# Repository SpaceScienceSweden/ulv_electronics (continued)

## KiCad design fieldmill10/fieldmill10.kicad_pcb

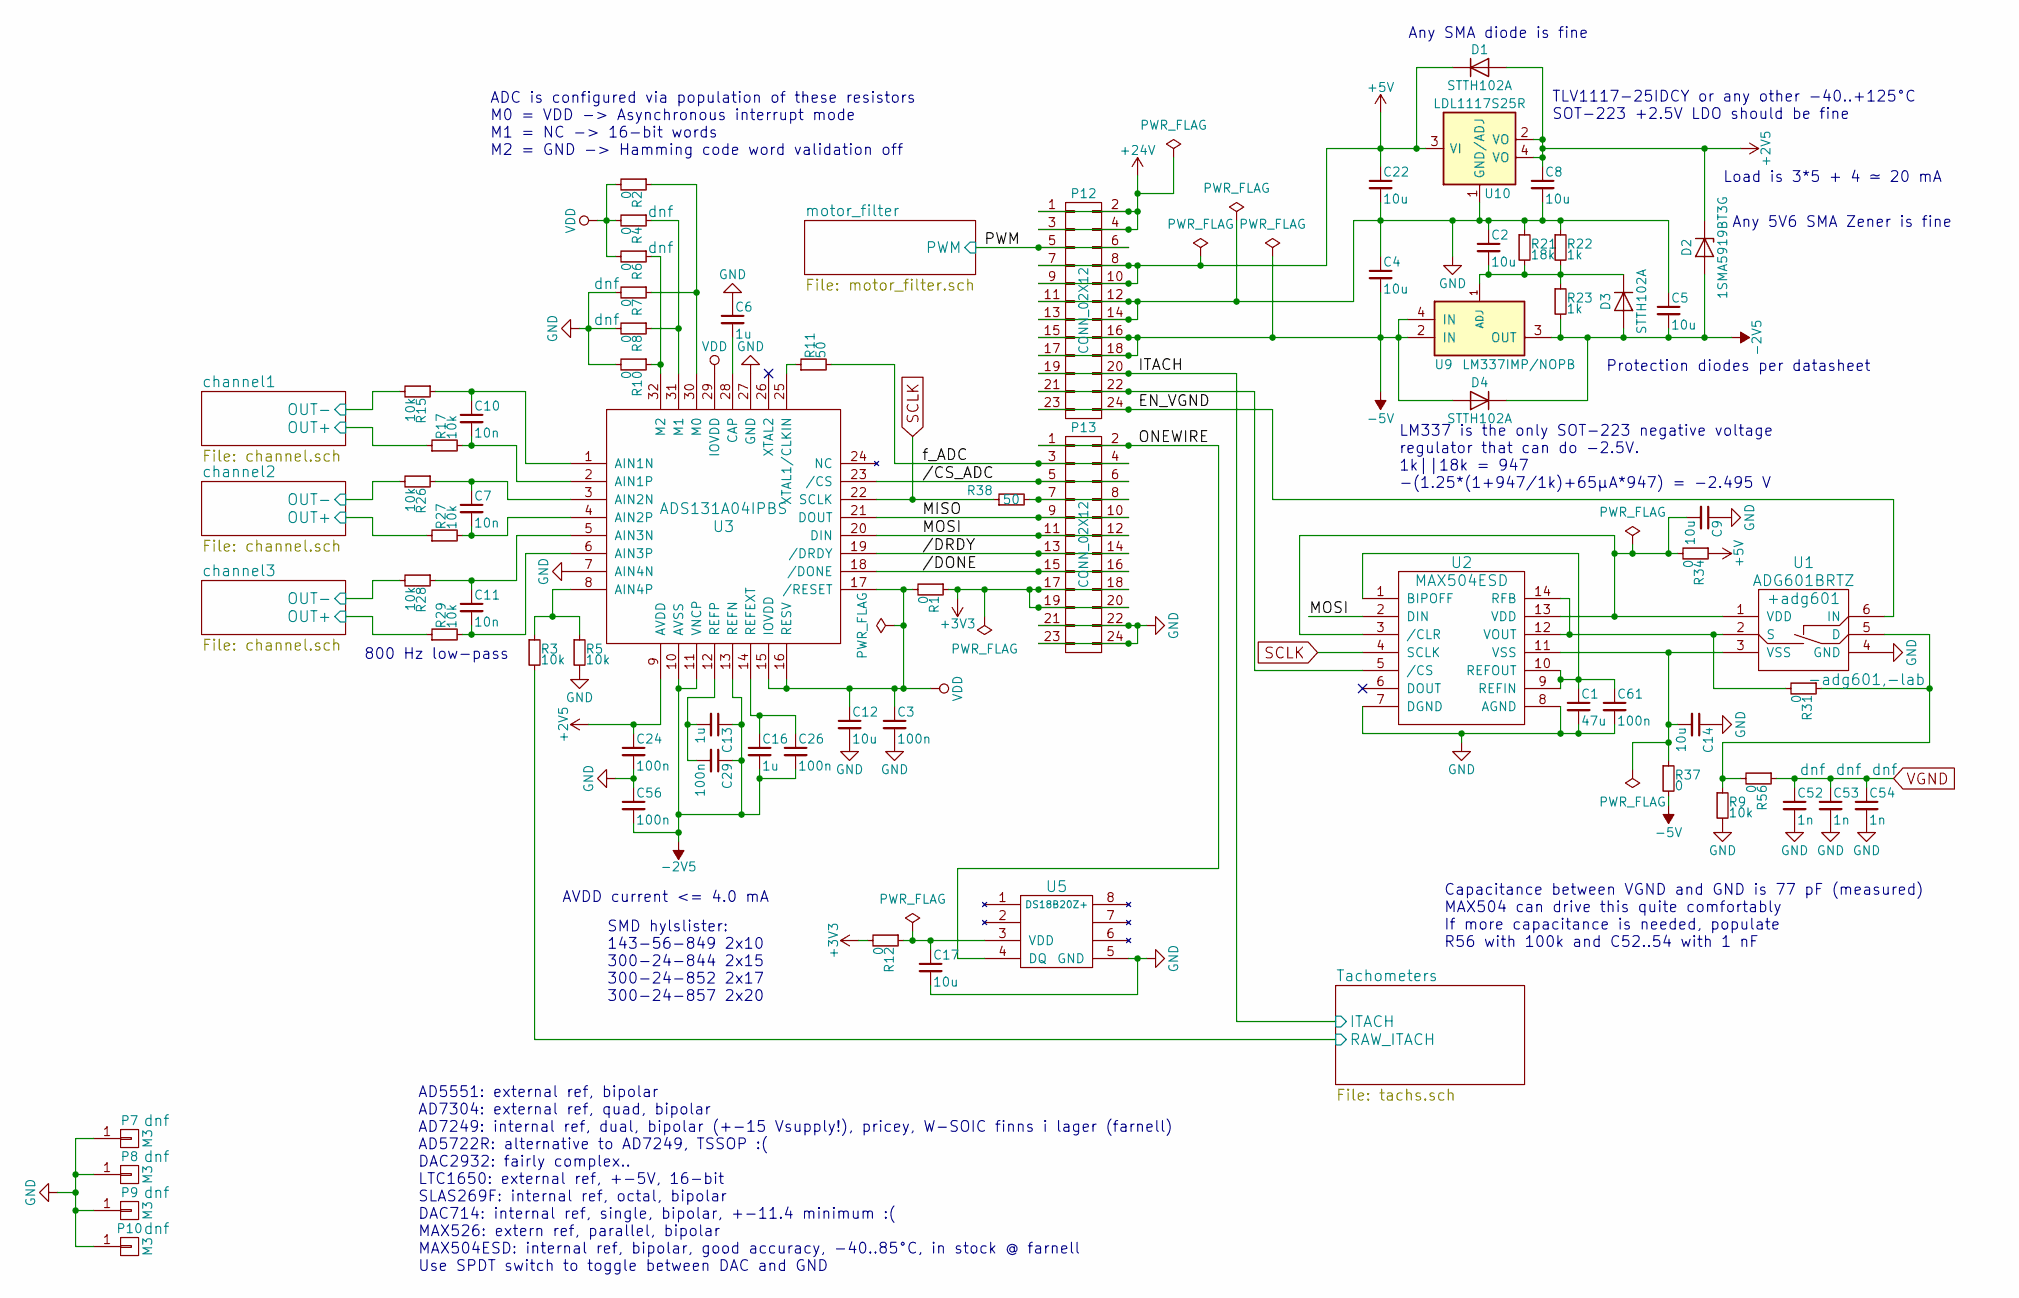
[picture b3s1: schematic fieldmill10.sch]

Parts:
C1: 47u; C_1210; Mfg. Part Number GCJ32ER70J476KE01L; Mouser PN 81-GCJ32ER70J476KE1L
C2, C4, C5, C9, C12, C14, C17, C22: 10u; C_0805; Mfg. Part Number C0805X106M8RACAUTO; Farnell PN 2776919
C3, C24, C26, C29, C56, C61: 100n; C_1210; Mfg. Part Number ECH-U1C104GX5; Farnell PN 9695001
C6, C13, C16: 1u; C_0805; Mfg. Part Number C0805X105K3RACAUTO; Farnell PN 2478267
C7, C10, C11: 10n; C_0805; Mfg. Part Number ECH-U1C103GX5; Farnell PN 9694897
C8: 10u; C_0805
C52, C53, C54: 1n; C_0805
D1, D3, D4: STTH102A; SMA_Standard; Mfg. Part Number STTH102A; Farnell PN 9907874
D2: 1SMA5919BT3G; SMA_Standard; Mfg. Part Number 1SMA5919BT3G; Farnell PN 1431141
P7, P8, P9, P10: M3; M3_FM_PTH
P12: CONN_02X12; LPPB122NFSP-RC-holes; Mfg. Part Number LPPB122NFSP-RC; Digikey PN S9007E-12-ND
P13: CONN_02X12; LPPB122NFSP-RC-holes
R1, R12, R34, R37: 0; R_1206
R2, R4, R6, R7, R8, R10, R31, R56: 0; R_0805
R3, R5, R9, R15, R17, R26, R27, R28, R29: 10k; R_0805
R11, R38: 50; R_0805
R21: 18k; R_0805
R22, R23: 1k; R_0805
U1: ADG601BRTZ; SOT-23-6; Mouser PN 584-ADG601BRTZ-R7; Farnell PN 1661035
U2: MAX504ESD; SOIC-14_3.9x8.7mm_Pitch1.27mm; Mfg. Part Number MAX504ESD+; Farnell PN 2514723
U3: ADS131A04IPBS; LQFP-32_5x5mm_Pitch0.5mm; Mfg. Part Number ADS131A04IPBS; Farnell PN 2580620
U5: DS18B20Z+; SOIC-8_3.9x4.9mm_Pitch1.27mm; Mfg. Part Number DS18B20Z+; Farnell PN 2518724
U9: LM337IMP/NOPB; SOT-223; Mfg. Part Number LM337IMP/NOPB; Farnell PN 2781817
U10: LDL1117S25R; SOT-223; Mfg. Part Number LDL1117S25R; Farnell PN 2778100

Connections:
+2V5: C8.1, C24.1, D1.2 (A), D2.1 (K), U3.9 (AVDD), U10.2 (VO), U10.4 (VO); also elsewhere on the board
+3V3: P13.17, P13.18, P13.19, P13.20, R1.1, R12.2; also elsewhere on the board
+5V: C22.1, D1.1 (K), P12.7, P12.8, P12.9, P12.10, R34.1, U10.3 (VI)
+24V: P12.1, P12.2, P12.3, P12.4; also elsewhere on the board
-2V5: C5.2, C13.1, C16.2, C26.2, C29.1, C56.2, D2.2 (A), D3.2 (A), D4.1 (K), R23.2, U3.10 (AVSS), U3.11 (VNCP), U3.13 (REFN), U9.3 (OUT); also elsewhere on the board
-5V: C4.2, D4.2 (A), P12.15, P12.16, P12.17, P12.18, R37.2, U9.2 (IN), U9.4 (IN); also elsewhere on the board
//CS_ADC: P13.5, P13.6, U3.23 (/CS)
//DONE: P13.15, P13.16, U3.18 (/DONE)
//DRDY: P13.13, P13.14, U3.19 (/DRDY)
/EN_VGND: P12.23, P12.24, U1.6 (IN)
/ITACH: P12.19, P12.20; also elsewhere on the board
/MISO: P13.9, P13.10, U3.21 (DOUT)
/MOSI: P13.11, P13.12, U2.2 (DIN), U3.20 (DIN)
/ONEWIRE: P13.1, P13.2, U5.4 (DQ)
/PWM: P12.5, P12.6; also elsewhere on the board
/Tachometers/RAW_ITACH: R3.2; also elsewhere on the board
/channel1/OUT+: R17.1; also elsewhere on the board
/channel1/OUT-: R15.2; also elsewhere on the board
/channel2/OUT+: R27.1; also elsewhere on the board
/channel2/OUT-: R26.2; also elsewhere on the board
/channel3/OUT+: R29.1; also elsewhere on the board
/channel3/OUT-: R28.2; also elsewhere on the board
/f_ADC: P13.3, P13.4, R11.2
GND: C1.2, C2.1, C3.2, C4.1, C5.1, C6.1, C8.2, C9.1, C12.2, C14.1, C17.2, C22.2, C24.2, C52.2, C53.2, C54.2, C56.1, C61.2, P7.1, P8.1, P9.1, P10.1, P12.11, P12.12, P12.13, P12.14, P13.21, P13.22, P13.23, P13.24, R5.2, R7.2, R8.2, R9.2, R10.2, R21.1, R22.1, U1.4 (GND), U2.7 (DGND), U2.8 (AGND), U3.7 (AIN4N), U3.27 (GND), U5.5 (GND), U10.1 (GND/ADJ); also elsewhere on the board
unnamed: C1.1, C61.1, U2.1 (BIPOFF), U2.9 (REFIN), U2.10 (REFOUT)
unnamed: C2.2, D3.1 (K), R21.2, R22.2, R23.1, U9.1 (ADJ)
unnamed: C6.2, U3.28 (CAP)
unnamed: C7.1, R26.1, U3.3 (AIN2N)
unnamed: C7.2, R27.2, U3.4 (AIN2P)
unnamed: C9.2, R34.2, U1.1 (VDD), U2.3 (/CLR), U2.13 (VDD)
unnamed: C10.1, R15.1, U3.1 (AIN1N)
unnamed: C10.2, R17.2, U3.2 (AIN1P)
unnamed: C11.1, R28.1, U3.5 (AIN3N)
unnamed: C11.2, R29.2, U3.6 (AIN3P)
unnamed: C13.2, C29.2, U3.12 (REFP)
unnamed: C14.2, R37.1, U1.3 (VSS), U2.11 (VSS)
unnamed: C16.1, C26.1, U3.14 (REFEXT)
unnamed: C17.1, R12.1, U5.3 (VDD)
unnamed: P12.21, P12.22, U2.5 (/CS)
unnamed: P13.7, P13.8, R38.2
unnamed: R2.1, R7.1, U3.30 (M0)
unnamed: R3.1, R5.1, U3.8 (AIN4P)
unnamed: R4.1, R8.1, U3.31 (M1)
unnamed: R6.1, R10.1, U3.32 (M2)
unnamed: R11.1, U3.25 (XTAL1/CLKIN)
unnamed: R9.1, R31.1, R56.2, U1.5 (D)
unnamed: R31.2, U1.2 (S), U2.12 (VOUT), U2.14 (RFB)
SCLK: R38.1, U2.4 (SCLK), U3.22 (SCLK)
VDD: C3.1, C12.1, R1.2, R2.2, R4.2, R6.2, U3.15 (IOVDD), U3.16 (RESV), U3.17 (/RESET), U3.29 (IOVDD)
VGND: C52.1, C53.1, C54.1, R56.1; also elsewhere on the board

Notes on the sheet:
ADC is configured via population of these resistors M0 = VDD -> Asynchronous interrupt mode M1 = NC -> 16-bit words M2 = GND -> Hamming code word validation off
800 Hz low-pass
SMD hylslister: 143-56-849 2x10 300-24-844 2x15 300-24-852 2x17 300-24-857 2x20
AVDD current <= 4.0 mA
AD5551: external ref, bipolar AD7304: external ref, quad, bipolar AD7249: internal ref, dual, bipolar (+-15 Vsupply!), pricey, W-SOIC finns i lager (farnell) AD5722R: alternative to AD7249, TSSOP :( DAC2932: fairly complex.. LTC1650: external ref, +-5V, 16-bit SLAS269F: internal ref, octal, bipolar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
Capacitance between VGND and GND is 77 pF (measured) MAX504 can drive this quite comfortably If more capacitance is needed, populate R56 with 100k and C52..54 with 1 nF
TLV1117-25IDCY or any other -40..+125°C SOT-223 +2.5V LDO should be fine
Load is 3*5 + 4 ≃ 20 mA
LM337 is the only SOT-223 negative voltage regulator that can do -2.5V. 1k||18k = 947 -(1.25*(1+947/1k)+65µA*947) = -2.495 V
Protection diodes per datasheet
Any SMA diode is fine
Any 5V6 SMA Zener is fine

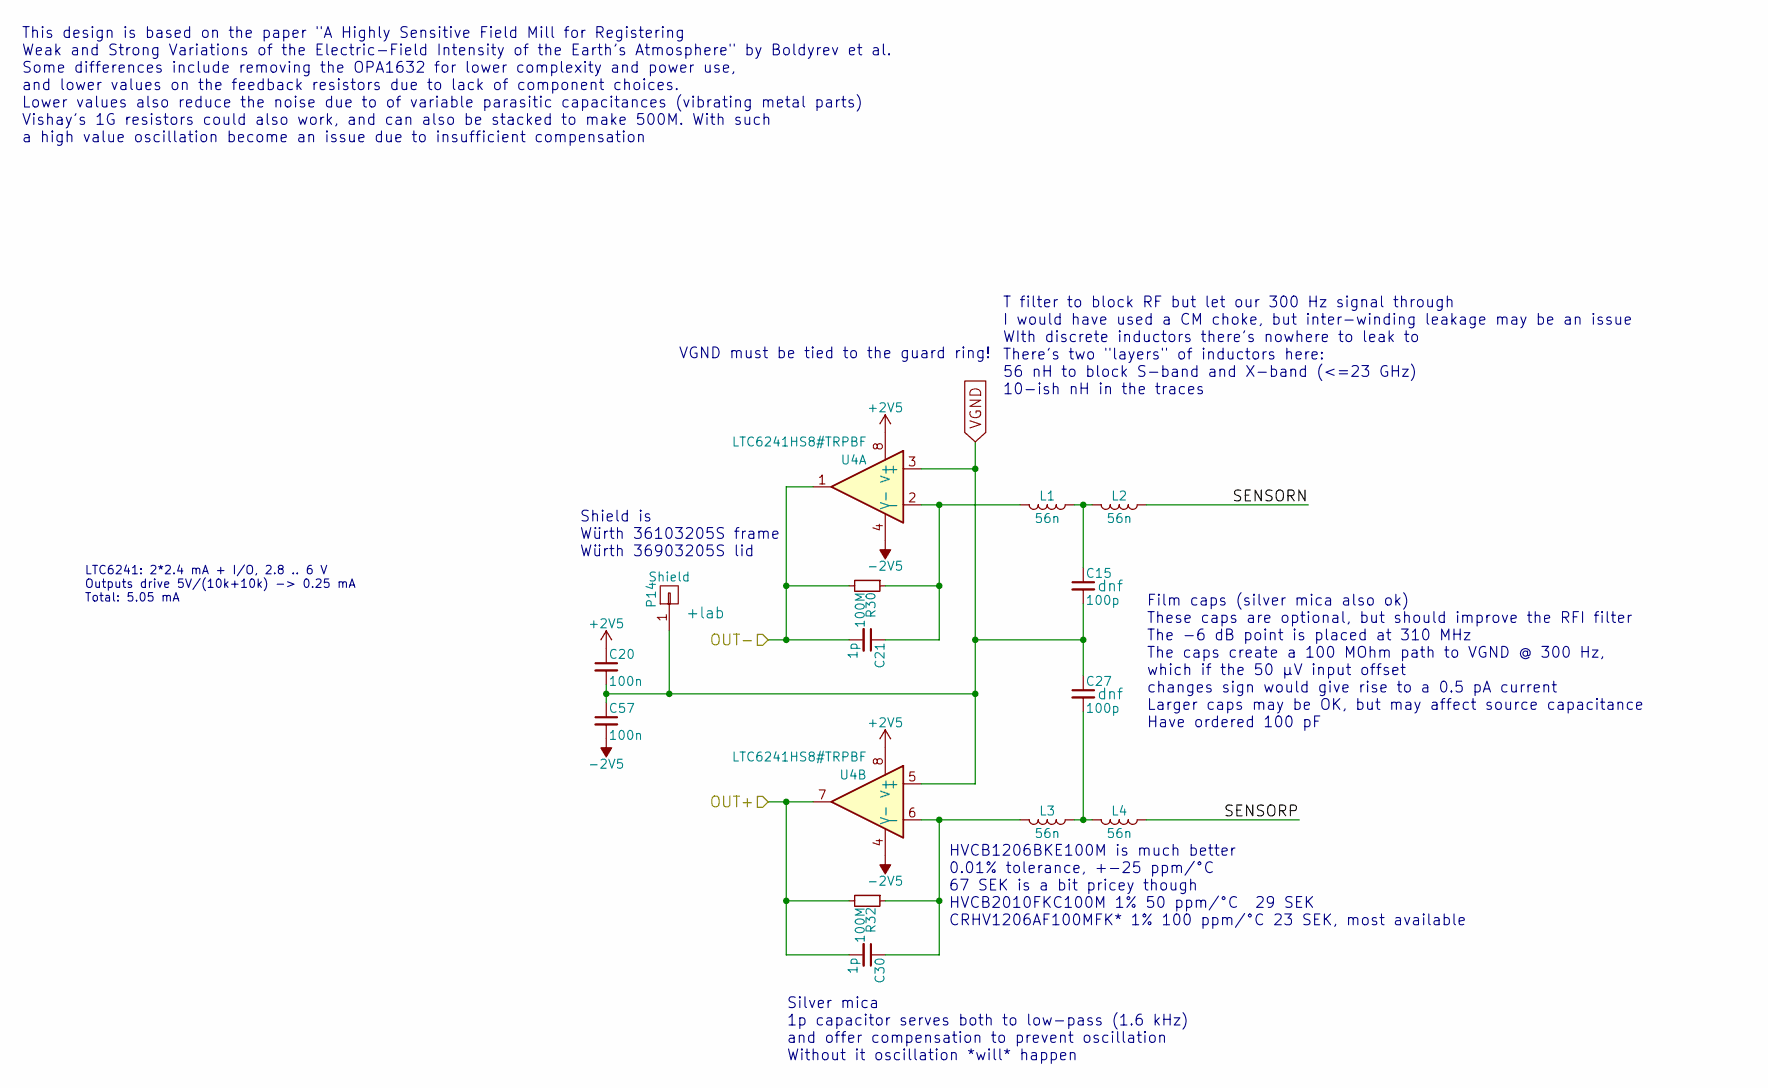
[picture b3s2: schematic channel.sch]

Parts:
C15, C27: 100p; C_0805; Mouser PN 667-ECH-U1H101GX5; Farnell PN 9695125
C20, C57: 100n; C_1210; Mfg. Part Number ECH-U1C104GX5; Farnell PN 9695001
C21, C30: 1p; C_0805; Mfg. Part Number MC08CA010D-F; Farnell PN 1610819
L1, L2, L3, L4: 56n; C_0603; Mfg. Part Number L-14C56NJV4T; Mouser PN 609-L-14C56NJV4T
P14: Shield; 36903205S
R30, R32: 100M; R_1206; Mfg. Part Number CRHV1206AF100MFK; Farnell PN 1109056
U4: LTC6241HS8#TRPBF; SOIC-8_3.9x4.9mm_Pitch1.27mm; Mfg. Part Number LTC6241HS8#TRPBF; Mouser PN 584-LTC6241HS8#TRPBF

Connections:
+2V5: C20.1, U4.8 (V+); also elsewhere on the board
-2V5: C57.2, U4.4 (V-); also elsewhere on the board
/channel1/OUT+: C30.2, R32.2, U4.7; also elsewhere on the board
/channel1/OUT-: C21.2, R30.2, U4.1; also elsewhere on the board
/channel1/SENSORN: L2.1
/channel1/SENSORP: L4.1
unnamed: C15.1, L1.1, L2.2
unnamed: C21.1, L1.2, R30.1, U4.2 (-)
unnamed: C27.2, L3.1, L4.2
unnamed: C30.1, L3.2, R32.1, U4.6 (-)
VGND: C15.2, C20.2, C27.1, C57.1, P14.1, U4.3 (+), U4.5 (+); also elsewhere on the board

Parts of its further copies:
C25, C28, C58, C59: 100n; C_1210; Mfg. Part Number ECH-U1C104GX5; Farnell PN 9695001
C32, C36, C38, C42: 1p; C_0805; Mfg. Part Number MC08CA010D-F; Farnell PN 1610819
C34, C41, C44, C45: 100p; C_0805; Mouser PN 667-ECH-U1H101GX5; Farnell PN 9695125
L5, L6, L7, L8, L9, L10, L11, L12: 56n; C_0603; Mfg. Part Number L-14C56NJV4T; Mouser PN 609-L-14C56NJV4T
P15, P16: Shield; 36903205S
R33, R35, R36, R42: 100M; R_1206; Mfg. Part Number CRHV1206AF100MFK; Farnell PN 1109056
U6, U8: LTC6241HS8#TRPBF; SOIC-8_3.9x4.9mm_Pitch1.27mm; Mfg. Part Number LTC6241HS8#TRPBF; Mouser PN 584-LTC6241HS8#TRPBF

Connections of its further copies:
+2V5: C25.1, C28.1, U6.8 (V+), U8.8 (V+); also elsewhere on the board
-2V5: C58.2, C59.2, U6.4 (V-), U8.4 (V-); also elsewhere on the board
/channel2/OUT+: C36.2, R33.2, U6.7; also elsewhere on the board
/channel2/OUT-: C32.2, R36.2, U6.1; also elsewhere on the board
/channel2/SENSORN: L6.1
/channel2/SENSORP: L8.1
/channel3/OUT+: C42.2, R35.2, U8.7; also elsewhere on the board
/channel3/OUT-: C38.2, R42.2, U8.1; also elsewhere on the board
/channel3/SENSORN: L10.1
/channel3/SENSORP: L12.1
unnamed: C32.1, L5.2, R36.1, U6.2 (-)
unnamed: C34.1, L5.1, L6.2
unnamed: C36.1, L7.2, R33.1, U6.6 (-)
unnamed: C38.1, L9.2, R42.1, U8.2 (-)
unnamed: C41.2, L7.1, L8.2
unnamed: C42.1, L11.2, R35.1, U8.6 (-)
unnamed: C44.1, L9.1, L10.2
unnamed: C45.2, L11.1, L12.2
VGND: C25.2, C28.2, C34.2, C41.1, C44.2, C45.1, C58.1, C59.1, P15.1, P16.1, U6.3 (+), U6.5 (+), U8.3 (+), U8.5 (+); also elsewhere on the board

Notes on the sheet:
This design is based on the paper "A Highly Sensitive Field Mill for Registering Weak and Strong Variations of the Electric-Field Intensity of the Earth’s Atmosphere" by Boldyrev et al. Some differences include removing the OPA1632 for lower complexity and power use, and lower values on the feedbac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
Silver mica 1p capacitor serves both to low-pass (1.6 kHz) and offer compensation to prevent oscillation Without it oscillation *will* happen
T filter to block RF but let our 300 Hz signal through I would have used a CM choke, but inter-winding leakage may be an issue WIth discrete inductors there's nowhere to leak to There's two "layers" of inductors here: 56 nH to block S-band and X-band (<=23 GHz) 10-ish nH in the traces
LTC6241: 2*2.4 mA + I/O, 2.8 .. 6 V Outputs drive 5V/(10k+10k) -> 0.25 mA Total: 5.05 mA
VGND must be tied to the guard ring!
Film caps (silver mica also ok) These caps are optional, but should improve the RFI filter The -6 dB point is placed at 310 MHz The caps create a 100 MOhm path to VGND @ 300 Hz, which if the 50 µV input offset changes sign would give rise to a 0.5 pA current Larger caps may be OK, but may affect so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
HVCB1206BKE100M is much better 0.01% tolerance, +-25 ppm/°C 67 SEK is a bit pricey though HVCB2010FKC100M 1% 50 ppm/°C 29 SEK CRHV1206AF100MFK* 1% 100 ppm/°C 23 SEK, most available
Shield is Würth 36103205S frame Würth 36903205S lid

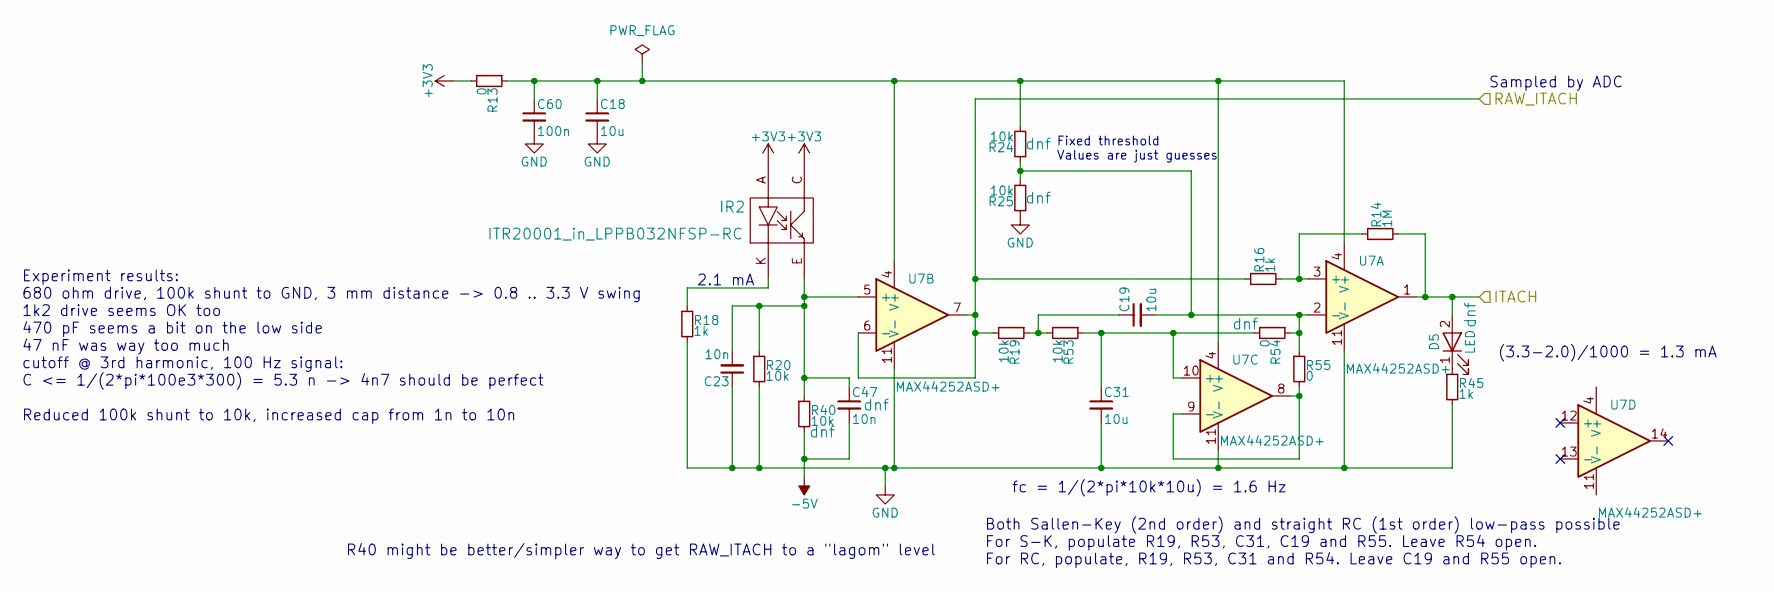
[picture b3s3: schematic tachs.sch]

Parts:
C18, C19, C31: 10u; C_0805; Mfg. Part Number C0805X106M8RACAUTO; Farnell PN 2776919
C23: 10n; C_0805; Mfg. Part Number ECH-U1C103GX5; Farnell PN 9694897
C47: 10n; C_0805
C60: 100n; C_1210; Mfg. Part Number ECH-U1C104GX5; Farnell PN 9695001
D5: LED; LED_0805
IR2: ITR20001_in_LPPB032NFSP-RC; LPPB032NFSP-RC-ITR20001; Mfg. Part Number LPPB032NFSP-RC; Digikey PN S9007E-03-ND
R13: 0; R_1206
R14: 1M; R_0805
R16, R18, R45: 1k; R_0805
R19, R20, R24, R25, R40, R53: 10k; R_0805
R54, R55: 0; R_0805
U7: MAX44252ASD+; SOIC-14_3.9x8.7mm_Pitch1.27mm; Mfg. Part Number MAX44252ASD+; Farnell PN 2510952

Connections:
+3V3: IR2.A, IR2.C, R13.2; also elsewhere on the board
-5V: C47.2, R40.2; also elsewhere on the board
/ITACH: D5.2 (A), R14.2, U7.1; also elsewhere on the board
/Tachometers/RAW_ITACH: R16.1, R19.2, U7.6 (-), U7.7; also elsewhere on the board
GND: C18.2, C23.1, C31.2, C60.2, R18.2, R20.2, R25.1, R45.2, U7.11 (V-); also elsewhere on the board
unnamed: C18.1, C60.1, R13.1, R24.2, U7.4 (V+)
unnamed: C19.1, R19.1, R53.2
unnamed: C19.2, R24.1, R25.2, R54.1, R55.1, U7.2 (-)
unnamed: C23.2, C47.1, IR2.E, R20.1, R40.1, U7.5 (+)
unnamed: C31.1, R53.1, R54.2, U7.10 (+)
unnamed: D5.1 (K), R45.1
unnamed: IR2.K, R18.1
unnamed: R14.1, R16.2, U7.3 (+)
unnamed: R55.2, U7.8, U7.9 (-)

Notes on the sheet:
fc = 1/(2*pi*10k*10u) = 1.6 Hz
R40 might be better/simpler way to get RAW_ITACH to a "lagom" level
(3.3-2.0)/1000 = 1.3 mA
Experiment results: 680 ohm drive, 100k shunt to GND, 3 mm distance -> 0.8 .. 3.3 V swing 1k2 drive seems OK too 470 pF seems a bit on the low side 47 nF was way too much cutoff @ 3rd harmonic, 100 Hz signal: C <= 1/(2*pi*100e3*300) = 5.3 n -> 4n7 should be perfect Reduced 100k shunt to 10k, increa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
Both Sallen-Key (2nd order) and straight RC (1st order) low-pass possible For S-K, populate R19, R53, C31, C19 and R55. Leave R54 open. For RC, populate, R19, R53, C31 and R54. Leave C19 and R55 open.
2.1 mA
Fixed threshold Values are just guesses
Sampled by ADC

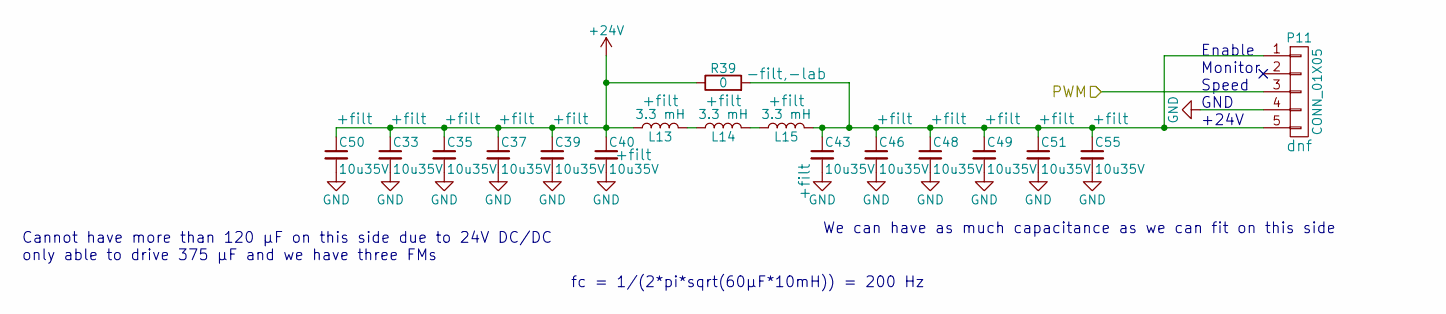
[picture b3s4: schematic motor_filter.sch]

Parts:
C33, C35, C37, C39, C40, C43, C46, C48, C49, C50, C51, C55: 10u35V; C_1206; Mfg. Part Number CGA5L1X7R1V106K160AE; Farnell PN 2547055
L13, L14, L15: 3.3 mH; Wurth_7687709332
P11: CONN_01X05; MOTOR_SMD
R39: 0; R_1206

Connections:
+24V: C33.1, C35.1, C37.1, C39.1, C40.1, C50.1, L13.1, R39.1; also elsewhere on the board
/PWM: P11.3; also elsewhere on the board
GND: C33.2, C35.2, C37.2, C39.2, C40.2, C43.2, C46.2, C48.2, C49.2, C50.2, C51.2, C55.2, P11.4; also elsewhere on the board
unnamed: C43.1, C46.1, C48.1, C49.1, C51.1, C55.1, L15.2, P11.1, P11.5, R39.2
unnamed: L13.2, L14.1
unnamed: L14.2, L15.1

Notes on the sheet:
Enable Monitor Speed GND +24V
fc = 1/(2*pi*sqrt(60µF*10mH)) = 200 Hz
Cannot have more than 120 µF on this side due to 24V DC/DC only able to drive 375 µF and we have three FMs
We can have as much capacitance as we can fit on this side

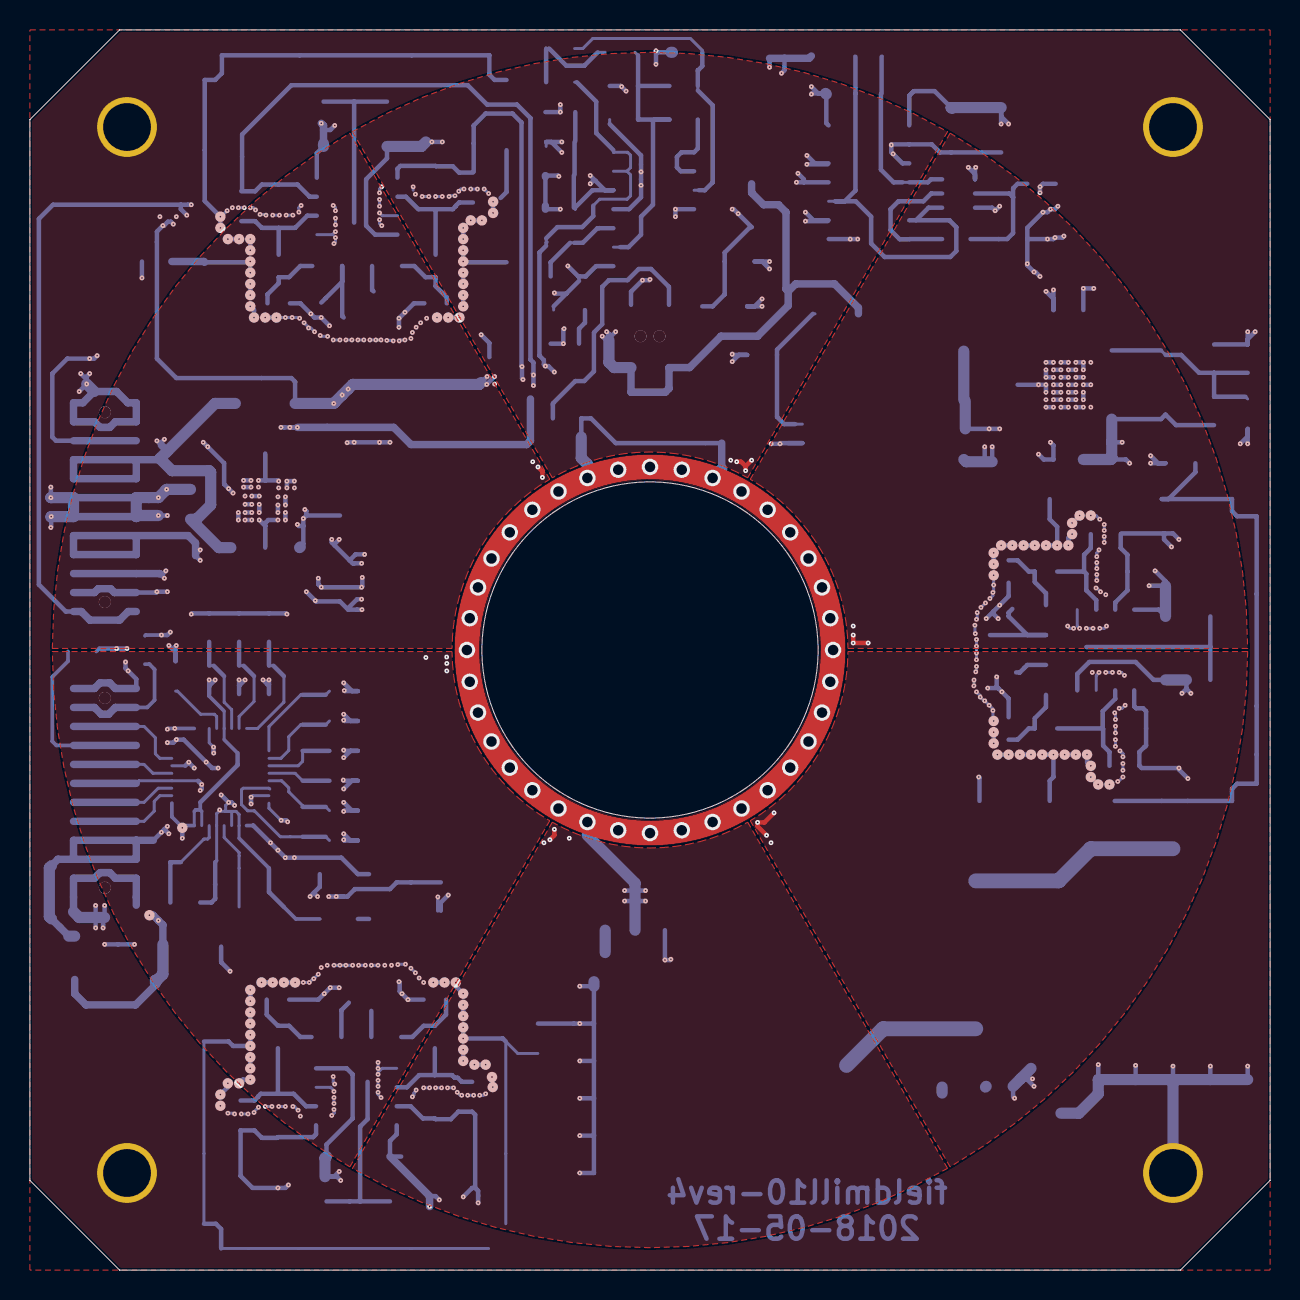
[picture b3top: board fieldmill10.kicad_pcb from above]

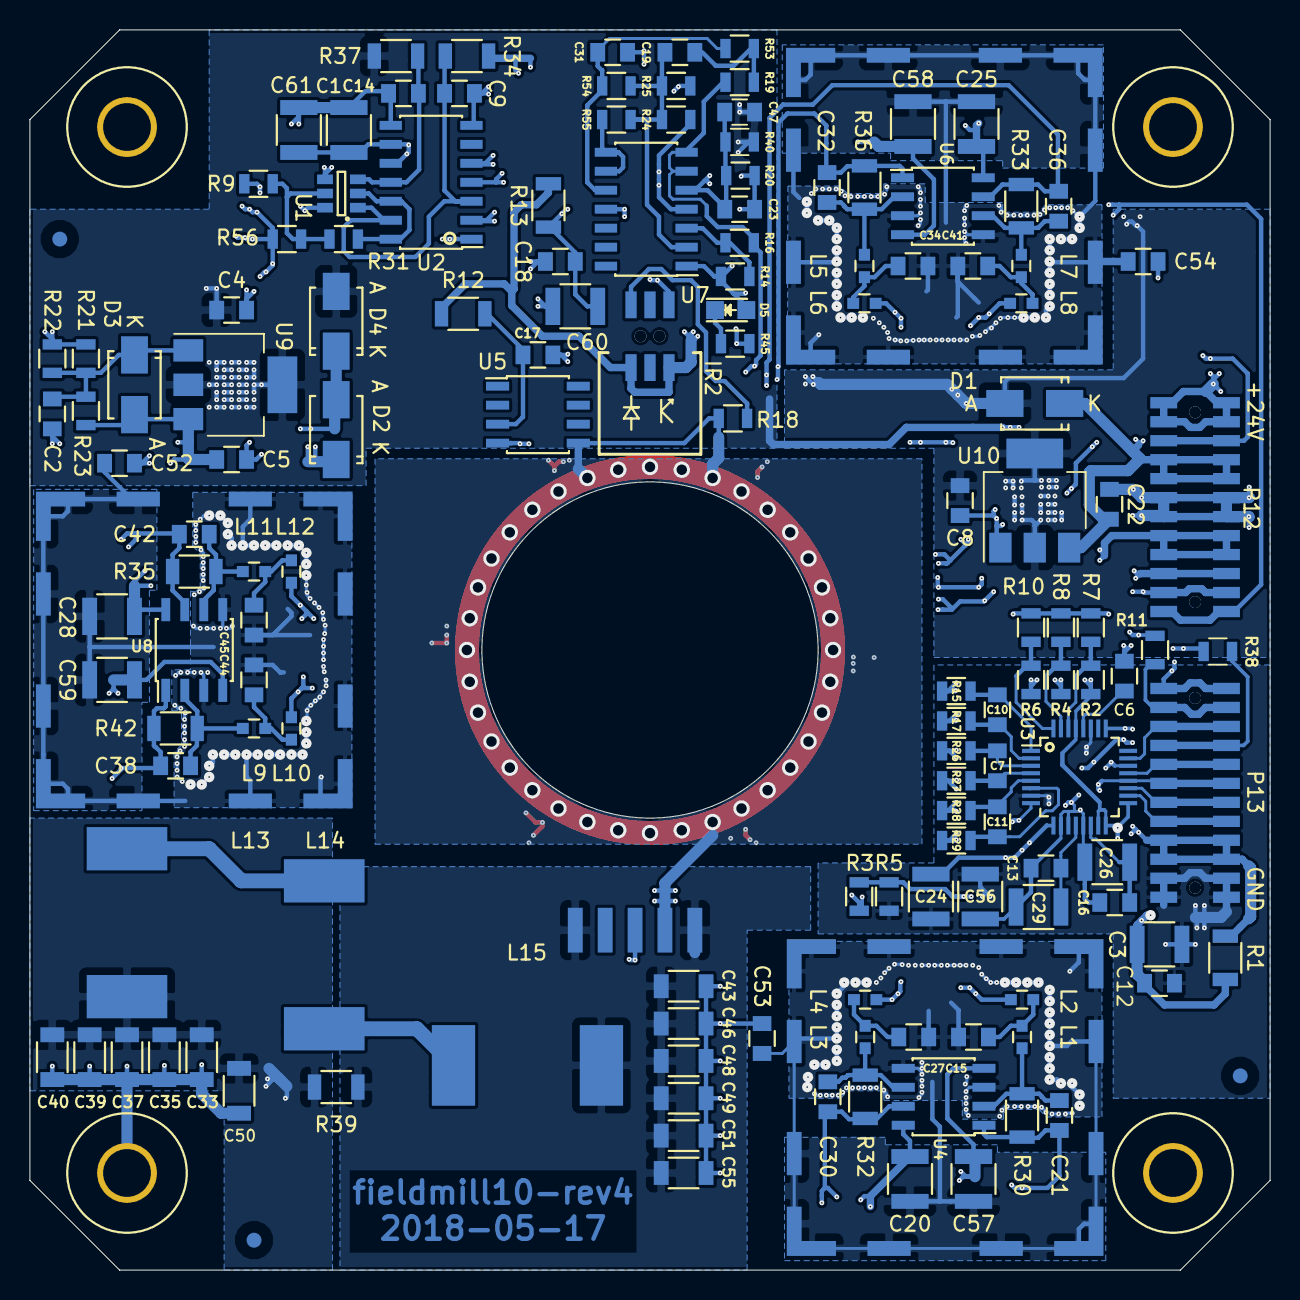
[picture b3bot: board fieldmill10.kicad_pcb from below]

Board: 6 copper layers, 83.0 x 83.0 mm, 151 parts (147 on the bottom side), 74 nets.

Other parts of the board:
REF1, REF2, REF3: Fiducial_1mm_Dia_2.54mm_Outer_CopperTop; Fiducial_1mm_Dia_2.54mm_Outer_CopperTop-paste

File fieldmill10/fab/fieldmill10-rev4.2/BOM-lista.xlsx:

|  | Design | Revision |  | Revisionshistorik
 |  | fieldmill10 | 4.2 | Grön = ändrad mellan 4.0 → 4.1 | 4.0 → 4.1: Ändrade 10 µF komponentval (item 3) Korrigerade Elfa artikelnr (item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
 |  |  |  | Blå = ändrad mellan 4.1 → 4.2 | 4.1 → 4.2: Ändrade färg på ändrade celler i item 13 till blå, för att signalera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
 | ITEM | Antal | Info | Position | Benämning Typ/värde | Tolerans/Spänning | Kapsel | Monteringssätt | Typbestämd | Generell | Förslag Leverantör | Leverantörs artikelnummer | Digikey PN | Farnell PN | Elfa PN | Mouser PN | Digikey Link | Farnell Link | Elfa Link
 | 1 | 13 |  | C3 C20 C24 C25 C26 C28 C29 C56 C57 C58 C59 C60 C61 | Cap film 100n | ±2% 16V PPS | C_1210 | SMD | x |  | Panasonic | ECH-U1C104GX5 | PCF1189CT-ND | 9695001 | 300-41-614 | 667-ECH-U1C104GX5 | https://www.digikey.se/product-detail/en/panasonic-electroni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 | https://se.farnell.com/panasonic-electronic-components/echu1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 | https://www.elfa.se/sv/kondensator-100-nf-16-vdc-panasonic-a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
 | 2 | 4 |  | C7 C10 C11 C23 | Cap film 10n | ±2% 16V PPS | C_0805 | SMD | x |  | Panasonic | ECH-U1C103GX5 | PCF1177CT-ND | 9694897 | 300-41-612 | 667-ECH-U1C103GX5 | https://www.digikey.se/product-detail/en/panasonic-electroni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 | https://se.farnell.com/panasonic-electronic-components/echu1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 | https://www.elfa.se/sv/kondensator-10-nf-16-vdc-panasonic-au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
 | 3 | 12 |  | C2 C4 C5 C8 C9 C12 C14 C17 C18 C19 C22 C31 | Cap cer 10u | ±20% 10V X7R soft termination or better | C_0805 | SMD | x |  | TDK | CGA4J1X7S1C106K125AE | 445-173674-1-ND |  |  | 810-CGA4J1X7S1C106KA | https://www.digikey.se/product-detail/en/tdk-corporation/CGA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
 | 4 | 6 |  | C21 C30 C32 C36 C38 C42 | Cap silver mica 1p | ±0.5pF 100V mica | C_0805 | SMD | x |  | Cornell Dubilier Electronics | MC08CA010D-F | 338-1339-ND | 1610819 |  | 5982-08-100V1.0-F | https://www.digikey.se/product-detail/en/cornell-dubilier-el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 | https://se.farnell.com/cornell-dubilier/mc08ca010d-f/capacit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
 | 5 | 3 |  | C6 C13 C16 | Cap cer 1u | ±10% 25V X7R soft termination | C_0805 | SMD | x |  | KEMET | C0805X105K3RACAUTO | 399-6996-1-ND | 2478267 |  | 80-C0805X105K3RAUTO | https://www.digikey.se/product-detail/en/kemet/C0805X105K3RA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 | https://se.farnell.com/kemet/c0805x105k3racauto/kondensator-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
 | 6 | 1 |  | C1 | Cap cer 47u | ±10% 6.3V X7R soft termination | C_1210 | SMD | x |  | Murata | GCJ32ER70J476KE01L | 490-10559-1-ND |  |  | 81-GCJ32ER70J476KE1L | https://www.digikey.se/product-detail/en/murata-electronics-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
 | 7 | 1 |  | D2 | 1SMA5919BT3G | ±5% 5.6V 1.5W | SMA_Standard | SMD | x |  | ON Semiconductor | 1SMA5919BT3G | 1SMA5919BT3GOSCT-ND | 1431141 | 300-50-189 | 863-1SMA5919BT3G | https://www.digikey.se/product-detail/en/on-semiconductor/1S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 | https://se.farnell.com/on-semiconductor/1sma5919bt3g/diode-z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 | https://www.elfa.se/sv/zenerdiod-sma-on-semiconductor-1sma59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
 | 8 | 3 |  | D1 D3 D4 | STTH102A | 1A 200V | SMA_Standard | SMD | x |  | STMicroelectronics | STTH102A | 497-2500-1-ND | 9907874 | 300-34-074 | 511-STTH102A | https://www.digikey.se/product-detail/en/stmicroelectronics/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 | https://se.farnell.com/stmicroelectronics/stth102a/diode-ult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 | https://www.elfa.se/sv/likriktardiod-sma-200-st-stth102a/p/30034074
 | 9 | 1 |  | IR2 | LPPB032NFSP-RC | Low outgassing, 50 mil | LPPB032NFSP-RC | SMD | x |  | Sullins | LPPB032NFSP-RC | S9007E-03-ND |  |  |  | https://www.digikey.com/product-detail/en/sullins-connector-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
 | 10 | 12 |  | L1 L2 L3 L4 L5 L6 L7 L8 L9 L10 L11 L12 | Ind chip 56n | Self res. >= 23GHz | C_0603 | SMD | x |  | Johanson | L-14C56NJV4T | 712-1443-1-ND |  |  | 609-L-14C56NJV4T | https://www.digikey.se/product-detail/en/johanson-technology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
 | 11 | 2 |  | P12 P13 | LPPB122NFSP-RC | Low outgassing, 50 mil | LPPB122NFSP-RC | SMD | x |  | Sullins | LPPB122NFSP-RC | S9007E-12-ND |  |  |  | https://www.digikey.com/products/en?keywords=LPPB122NFSP-RC
 | 12 | 6 |  | R1 R12 R13 R34 R37 R39 | 0 | Jumper | R_1206 | SMD |  | x
 | 13 | 5 |  | R2 R10 R31 R55 R56 | 0 | Jumper | R_0805 | SMD |  | x
 | 14 | 6 |  | R30 R32 R33 R35 R36 R42 | 100M | 1%, ±100ppm/°C | R_1206 | SMD | x |  | Vishay | CRHV1206AF100MFK | CRHV100MACT-ND | 1109056 |  | 71-CRHV1206AF100MFKF | https://www.digikey.se/product-detail/en/vishay-dale/CRHV120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 | https://se.farnell.com/vishay/crhv1206af100mfkft/motst-tunnf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
 | 15 | 12 |  | R3 R5 R9 R15 R17 R19 R20 R26 R27 R28 R29 R53 | 10k | 1% | R_0805 | SMD |  | x
 | 16 | 1 |  | R21 | 18k | 1% | R_0805 | SMD |  | x
 | 17 | 1 |  | R14 | 1M | 1% | R_0805 | SMD |  | x
 | 18 | 5 |  | R16 R18 R22 R23 R45 | 1k | 1% | R_0805 | SMD |  | x
 | 19 | 2 |  | R11 R38 | 49,9 | 1% | R_0805 | SMD |  | x
 | 20 | 1 |  | U3 | ADS131A04IPBS | -40°C .. +125°C industrial | LQFP-32_5x5mm_Pitch0.5mm | SMD | x |  | Texas Instruments | ADS131A04IPBS | 296-47690-ND | 2580620 |  | 595-ADS131A04IPBS | https://www.digikey.se/product-detail/en/texas-instruments/A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 | https://se.farnell.com/texas-instruments/ads131a04ipbsr/adc-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
 | 21 | 1 |  | U5 | DS18B20Z+ | -55°C .. +125°C | SOIC-8_3.9x4.9mm_Pitch1.27mm | SMD | x |  | Maxim Integrated | DS18B20Z+ | DS18B20Z+-ND | 2518724 |  | 700-DS18B20Z | https://www.digikey.se/product-detail/en/maxim-integrated/DS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 | https://se.farnell.com/maxim-integrated-products/ds18b20z/ic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
 | 22 | 1 |  | U10 | LDL1117S25R | -40°C .. +125°C | SOT-223 | SMD | x |  | STMicroelectronics | LDL1117S25R | 497-17237-1-ND | 2778100 |  | 511-LDL1117S25R | https://www.digikey.se/product-detail/en/stmicroelectronics/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 | https://se.farnell.com/stmicroelectronics/ldl1117s25r/ldo-fi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
 | 23 | 1 |  | U9 | LM337IMP/NOPB | -40°C .. +125°C industrial | SOT-223 | SMD | x |  | Texas Instruments | LM337IMP/NOPB | LM337IMP/NOPBCT-ND | 2781817 | 173-28-875 | 926-LM337IMP/NOPB | https://www.digikey.se/product-detail/en/texas-instruments/L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 | https://se.farnell.com/texas-instruments/lm337imp-nopb/linea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 | https://www.elfa.se/sv/spaenningsregulator-37-sot-223-lm337-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
 | 24 | 3 |  | U4 U6 U8 | LTC6241HS8#TRPBF | -40°C .. +125°C industrial | SOIC-8_3.9x4.9mm_Pitch1.27mm | SMD | x |  | Linear Technology/Analog Devices | LTC6241HS8#TRPBF | LTC6241HS8#TRPBFCT-ND |  |  | 584-LTC6241HS8#TRPBF | https://www.digikey.com/product-detail/en/linear-technology-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
 | 25 | 1 |  | U7 | MAX44252ASD+ | -40°C .. +125°C | SOIC-14_3.9x8.7mm_Pitch1.27mm | SMD | x |  | Maxim Integrated | MAX44252ASD+ | MAX44252ASD+-ND | 2510952 |  | 700-MAX44252ASD+ | https://www.digikey.se/product-detail/en/maxim-integrated/MA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 | https://se.farnell.com/maxim-integrated-products/max44252asd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
 | 26 | 1 |  | U2 | MAX504ESD | -40°C .. +85°C | SOIC-14_3.9x8.7mm_Pitch1.27mm | SMD | x |  | Maxim Integrated | MAX504ESD+ | MAX504ESD+-ND | 2514723 |  | 700-MAX504ESD | https://www.digikey.se/product-detail/en/maxim-integrated/MA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 | https://se.farnell.com/maxim-integrated-products/max504esd/d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
